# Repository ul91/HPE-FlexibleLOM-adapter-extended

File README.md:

HPE FlexibleLOM to PCIe adapter extended
========================================

This PCB is an extended adapter of the [orginal version](https://github.com/TobleMiner/HPE-FlexibleLOM-adapter) created by [TobleMiner](https://github.com/TobleMiner), that allows using HPE FlexibleLOM cards in normal PCIe x8 slots.

German blogentry: https://npserver.de/HPEFlexibleLOM

# Ordering

Make sure to order this PCB with ENIG finish and beveled edges. Else contact
might be poor or your PCIe slots could be damaged.  
When ordering through JLC I'd recommend enabling the "Impedance" option and
sticking to the default JLC7628 stackup during ordering.

# Assembly

The board requires just a stradle mount PCIe x8 connector to be fitted.
You can get it at LCSC: [C404097](https://lcsc.com/product-detail/Card-Edge-Connectors_UMAX-3126-10102T_C404097.html)

# Mechanical mounting

This board has been designed to bring the front FlexibleLOM mounting hole as
close as possible to the PCIe bracket retention screw on a full size PCIe slot.
You can use a small angled metal piece or a even a 3d printed one to mount the
card into place.

# Jumpers

This adapter cards has several jumpers. You should not need to touch them, however
the following sections will explain their purpose.

## PERST

This jumper selects where the PCIe reset signal is routed. By default it is routed
to A1 on the FlexibleLOM slot. I believe this to be the PCIe reset signal. However,
there is also another pin on the connector, A14 which behaves similarly to A1.  
Testing has shown that the cards does not always enumerate properly when using A14
as PCIe reset.  
The two resistor footprints next to this jumper can be populated in case you are
having issues with floating resets on the cards resulting in spurious resets. I
have not encountered any such issues.

## Vdet

The Vdet jumper bridges +12V to pin B1 on the FlexibleLOM slot. I assume B1 to be
some sort of voltage detection pin since it is routed very differently from all
other +12V power signals on the card.

## 3v3 aux

The 3v3 aux jumper connects what I think is the auxiliary 3v3 volt voltage supply
on the FlexibleLOM slot to the auxiliary 3v3 supply of the PCIe connector. Most
cards I've seen do not use this voltage rail. However I assume there might be some
that utilize it for WOL capability.

## lanes

This jumper controls which PRSNT2 pin is bridged to PRSNT1. It defaults to PRSNT2
for 8x cards since that is the maximum number of lanes on a FlexibleLOM slot. You
can try setting this jumper to 4x if you are having issues with card detection.  
However, a lot of modern devices tend to ignore the PRSNT2 line and rely solely on
detecting the lane transmitters/receivers. Thus this setting will be irrelevant for
most devices.

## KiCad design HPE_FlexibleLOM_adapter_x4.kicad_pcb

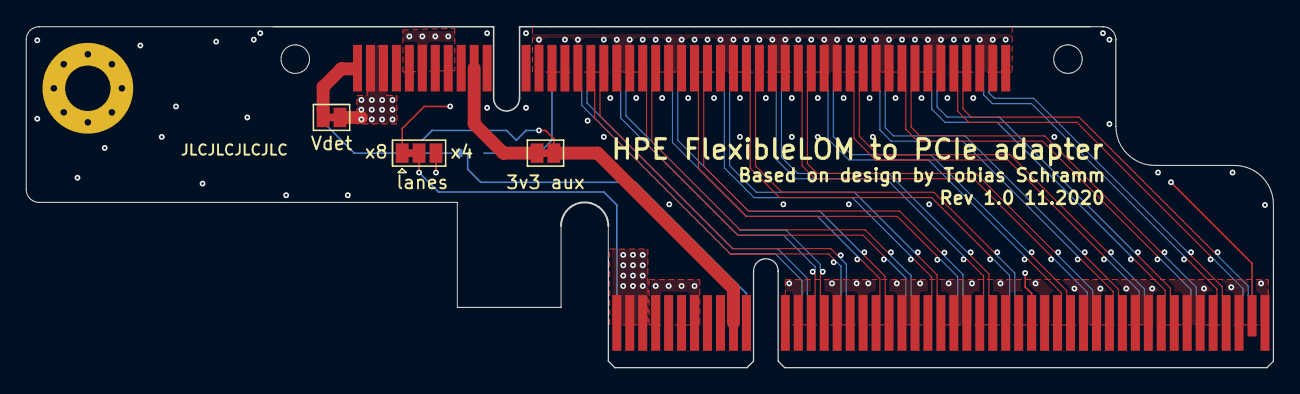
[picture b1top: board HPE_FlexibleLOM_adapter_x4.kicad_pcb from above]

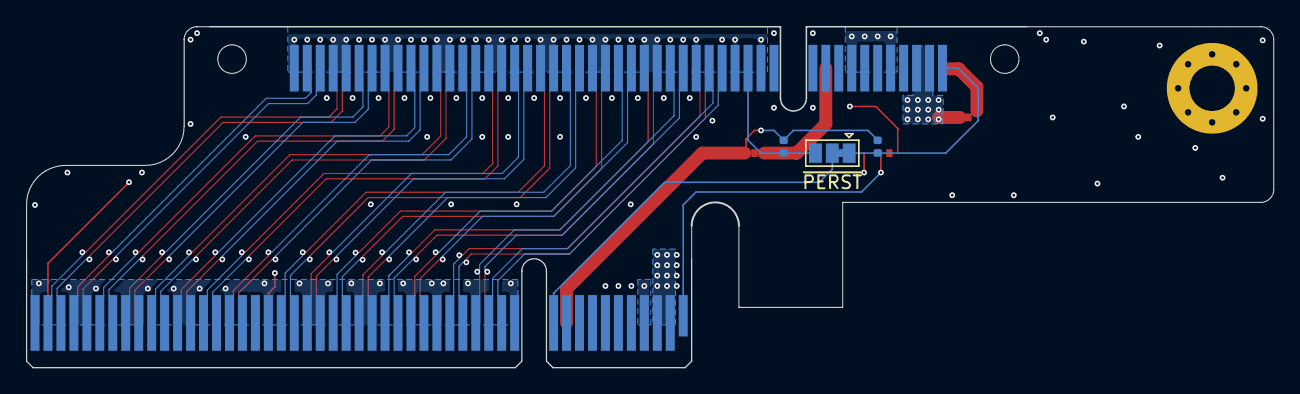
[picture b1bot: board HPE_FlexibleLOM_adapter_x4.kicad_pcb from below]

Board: 4 copper layers, 96.2 x 26.3 mm, 8 parts (3 on the bottom side), 45 nets.

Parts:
J1: Connector_PCIe_x8; BUS_PCIexpress_x8
J2: HPE_FlexibleLOM_x8; UMAX_3126-10102T_PCIe_x8_edge_launch
JP1, JP2: Jumper_NC_Small; SolderJumper-2_P1.3mm_Bridged_Pad1.0x1.5mm
JP3, JP4: Jumper_3_Bridged12; SolderJumper-3_P1.3mm_Bridged12_Pad1.0x1.5mm
R1, R2: 100kR; R_0402_1005Metric

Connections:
+3V3: J1.B10, JP1.1, R1.2, R2.2
+12V: J1.A2, J1.A3, J1.B1, J1.B2, J1.B3, J2.A2, J2.A3, J2.B2, J2.B3, JP2.1
/PRSNT_x4: J1.B31, JP4.3
/PRSNT_x8: J1.B48, JP4.1
/REFCLK+: J1.A13, J2.A16
/REFCLK-: J1.A14, J2.A17
/RX0+: J1.A16, J2.B17
/RX0-: J1.A17, J2.B18
/RX1+: J1.A21, J2.B21
/RX1-: J1.A22, J2.B22
/RX2+: J1.A25, J2.B25
/RX2-: J1.A26, J2.B26
/RX3+: J1.A29, J2.B29
/RX3-: J1.A30, J2.B30
/RX4+: J1.A35, J2.B33
/RX4-: J1.A36, J2.B34
/RX5+: J1.A39, J2.B37
/RX5-: J1.A40, J2.B38
/RX6+: J1.A43, J2.B41
/RX6-: J1.A44, J2.B42
/RX7+: J1.A47, J2.B45
/RX7-: J1.A48, J2.B46
/TX0+: J1.B14, J2.A19
/TX0-: J1.B15, J2.A20
/TX1+: J1.B19, J2.A23
/TX1-: J1.B20, J2.A24
/TX2+: J1.B23, J2.A27
/TX2-: J1.B24, J2.A28
/TX3+: J1.B27, J2.A31
/TX3-: J1.B28, J2.A32
/TX4+: J1.B33, J2.A35
/TX4-: J1.B34, J2.A36
/TX5+: J1.B37, J2.A39
/TX5-: J1.B38, J2.A40
/TX6+: J1.B41, J2.A43
/TX6-: J1.B42, J2.A44
/TX7+: J1.B45, J2.A47
/TX7-: J1.B46, J2.A48
/~PERST: J1.A11, JP3.2
GND: J1.A4, J1.A12, J1.A15, J1.A18, J1.A20, J1.A23, J1.A24, J1.A27, J1.A28, J1.A31, J1.A34, J1.A37, J1.A38, J1.A41, J1.A42, J1.A45, J1.A46, J1.A49, J1.B4, J1.B7, J1.B13, J1.B16, J1.B18, J1.B21, J1.B22, J1.B25, J1.B26, J1.B29, J1.B32, J1.B35, J1.B36, J1.B39, J1.B40, J1.B43, J1.B44, J1.B47, J1.B49, J2.A5, J2.A8, J2.A13, J2.A15, J2.A18, J2.A21, J2.A22, J2.A25, J2.A26, J2.A29, J2.A30, J2.A33, J2.A34, J2.A37, J2.A38, J2.A41, J2.A42, J2.A45, J2.A46, J2.A49, J2.B6, J2.B13, J2.B16, J2.B19, J2.B20, J2.B23, J2.B24, J2.B27, J2.B28, J2.B31, J2.B32, J2.B35, J2.B36, J2.B39, J2.B40, J2.B43, J2.B44, J2.B47, J2.B48
unnamed: J1.A1, JP4.2
unnamed: J2.A1, JP3.1, R1.1
unnamed: J2.A14, JP3.3, R2.1
unnamed: J2.B1, JP2.2
unnamed: J2.B10, JP1.2
